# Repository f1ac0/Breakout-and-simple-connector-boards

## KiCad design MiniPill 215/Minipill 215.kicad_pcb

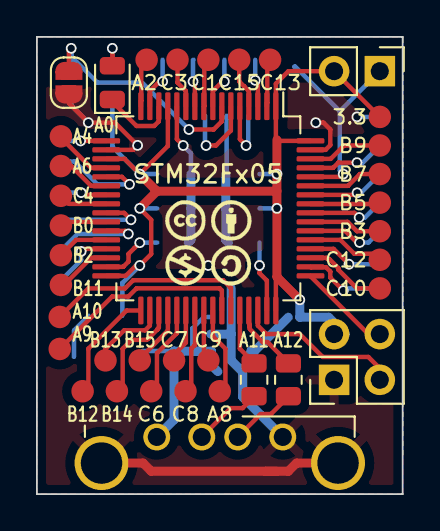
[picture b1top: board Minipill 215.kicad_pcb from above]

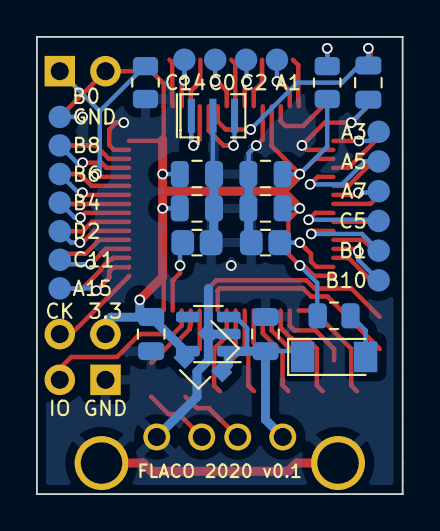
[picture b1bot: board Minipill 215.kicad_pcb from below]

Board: 2 copper layers, 20.3 x 25.4 mm, 71 parts (33 on the bottom side), 62 nets.

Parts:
C1, C2: 10u; C_0805_2012Metric
C3, C4, C5, C6, C7: 100n; C_0805_2012Metric
C10, C11: 2.2u; C_0805_2012Metric_shortable
D1: Zener 3.3v; D_MiniMELF
D2: LED; LED_0805_2012Metric
J1: Boot0; PinHeader_1x02_P2.54mm_Vertical
J2: USB_A; USB_A_female_THT_G54
J3: PROG; PinHeader_2x02_P2.54mm_Vertical
JP1: NRST; SolderJumper-2_P1.3mm_Open_RoundedPad1.0x1.5mm
MK5: License; CC_BY_NC_SA_square_silkscreen_4.8x4.8mm
R1, R2: 22; R_0805_2012Metric
R4: 4700; R_0805_2012Metric
R5: R_Small; R_0805_2012Metric
R6: 1k; R_0805_2012Metric
TP1, TP3, TP4, TP5, TP6, TP7, TP8, TP9, TP10, TP11, TP12, TP13, TP14, TP15, TP16, TP17, TP18, TP19, TP20, TP21, TP22, TP23, TP24, TP25, TP26, TP27, TP28, TP29, TP30, TP31, TP32, TP33, TP34, TP35, TP36, TP37, TP38, TP39, TP40, TP41, TP42, TP43, TP45, TP46: TP; Measurement_Point_Round-SMD-Pad_VerySmall
TP2: RX; Measurement_Point_Round-SMD-Pad_VerySmall
TP44: TX; Measurement_Point_Round-SMD-Pad_VerySmall
U1: STM32F105R8Tx; LQFP-64_10x10mm_P0.5mm
U2: SPX3819M5-L-3-3; SOT-23-5
U3: XC6206PxxxMR; SOT-23
Y1: 8MHz; Resonator_SMD_Murata_CSTxExxV-3Pin_3.0x1.1mm

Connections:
+3.3V: C2.1, C4.1, C5.1, C6.1, C7.1, J1.2, J3.2, R5.1, R6.1, TP45.1, U1.1 (VBAT), U1.13 (VDDA), U1.19 (VDD), U1.32 (VDD), U1.48 (VDD), U1.64 (VDD), U2.5 (OUT), U3.2 (VO)
+5V: C1.1, D1.1 (K), J2.1 (VBUS), U2.1 (IN), U2.3 (EN), U3.3 (VI)
BOOT0: J1.1, R4.1, U1.60 (BOOT0)
GROUND: C1.2, C2.2, C3.2, C4.2, C5.2, C6.2, C7.2, C10.2, C11.2, J2.4 (GND), J2.5 (Shield), J3.1, JP1.2 (B), R4.2, TP46.1, U1.12 (VSSA), U1.18 (VSS), U1.63 (VSS), U2.2 (GND), U3.1 (GND), Y1.2
JTCK-SWCLK: J3.4, U1.49 (PA14)
JTMS-SWDIO: J3.3, U1.46 (PA13)
LED: D2.1 (K), U1.14 (PA0)
NRST: C3.1, JP1.1 (A), U1.7 (NRST)
unnamed: U1.5 (PD0), Y1.1
unnamed: U1.6 (PD1), Y1.3
unnamed: C10.1, U1.31 (VSS)
unnamed: C11.1, U1.47 (VSS)
unnamed: D1.2 (A), R5.2
unnamed: D2.2 (A), R6.2
unnamed: J2.2 (D-), R2.1
unnamed: J2.3 (D+), R1.1
unnamed: TP1.1, U1.54 (PD2)
unnamed: TP3.1, U1.8 (PC0)
unnamed: TP4.1, U1.9 (PC1)
unnamed: TP5.1, U1.10 (PC2)
unnamed: TP6.1, U1.11 (PC3)
unnamed: TP7.1, U1.24 (PC4)
unnamed: TP8.1, U1.25 (PC5)
unnamed: TP9.1, U1.37 (PC6)
unnamed: TP10.1, U1.38 (PC7)
unnamed: TP11.1, U1.39 (PC8)
unnamed: TP12.1, U1.40 (PC9)
unnamed: TP13.1, U1.51 (PC10)
unnamed: TP14.1, U1.52 (PC11)
unnamed: TP15.1, U1.53 (PC12)
unnamed: TP16.1, U1.2 (PC13)
unnamed: TP17.1, U1.3 (PC14)
unnamed: TP18.1, U1.4 (PC15)
unnamed: TP19.1, U1.15 (PA1)
unnamed: TP20.1, U1.16 (PA2)
unnamed: TP21.1, U1.17 (PA3)
unnamed: TP22.1, U1.20 (PA4)
unnamed: TP23.1, U1.21 (PA5)
unnamed: TP24.1, U1.22 (PA6)
unnamed: TP25.1, U1.23 (PA7)
unnamed: TP26.1, U1.41 (PA8)
unnamed: TP27.1, U1.50 (PA15)
unnamed: TP28.1, U1.26 (PB0)
unnamed: TP29.1, U1.27 (PB1)
unnamed: TP30.1, U1.28 (PB2)
unnamed: TP31.1, U1.55 (PB3)
unnamed: TP32.1, U1.56 (PB4)
unnamed: TP33.1, U1.57 (PB5)
unnamed: TP34.1, U1.58 (PB6)
unnamed: TP35.1, U1.59 (PB7)
unnamed: TP36.1, U1.61 (PB8)
unnamed: TP37.1, U1.62 (PB9)
unnamed: TP38.1, U1.29 (PB10)
unnamed: TP39.1, U1.30 (PB11)
unnamed: TP40.1, U1.33 (PB12)
unnamed: TP41.1, U1.34 (PB13)
unnamed: TP42.1, U1.35 (PB14)
unnamed: TP43.1, U1.36 (PB15)
OTG_FS_DM: R2.2, U1.44 (PA11)
OTG_FS_DP: R1.2, U1.45 (PA12)
RX: TP2.1, U1.43 (PA10)
TX: TP44.1, U1.42 (PA9)

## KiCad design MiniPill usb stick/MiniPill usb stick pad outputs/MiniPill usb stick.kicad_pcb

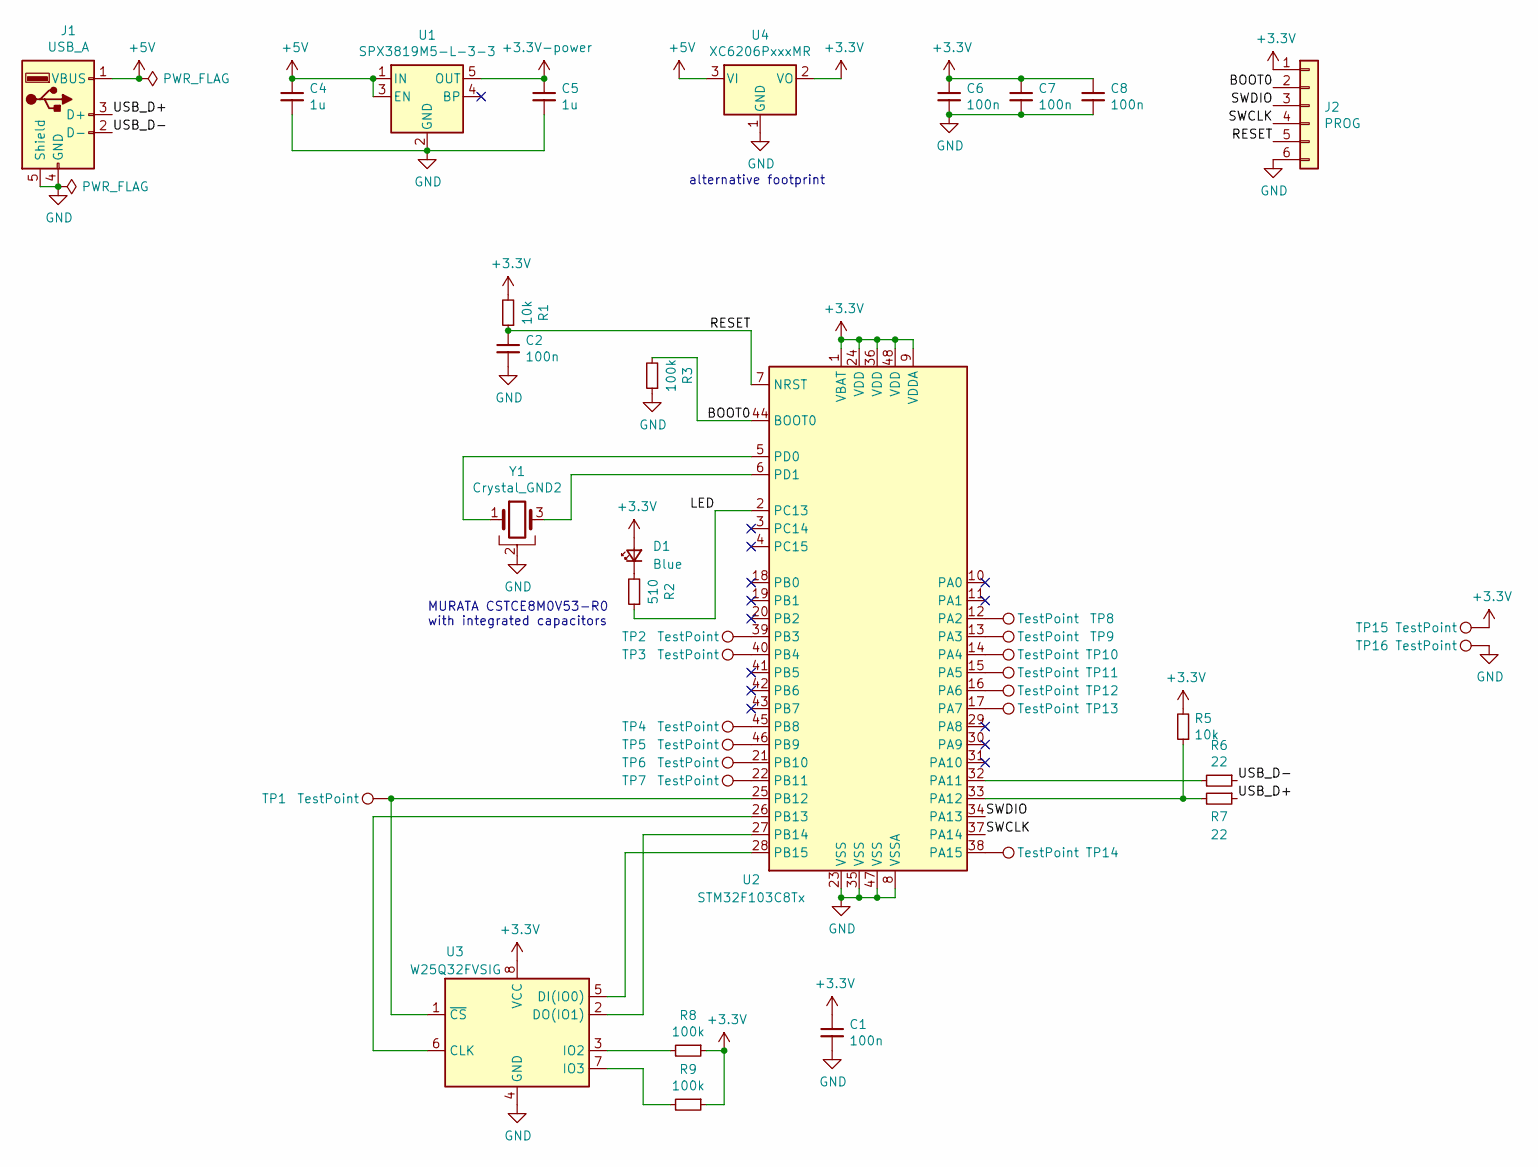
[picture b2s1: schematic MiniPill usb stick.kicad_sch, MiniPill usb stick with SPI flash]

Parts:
C1, C2, C6, C7, C8: 100n; C_0805_2012Metric
C4, C5: 1u; C_0805_2012Metric
D1: Blue; LED_0805_2012Metric
J1: USB_A; USB_A_CNCTech_1001-011-01101_Horizontal
J2: PROG; PinHeader_1x08_P2.54mm_Vertical
R1, R5: 10k; R_0805_2012Metric
R2: 510; R_0805_2012Metric
R3, R8, R9: 100k; R_0805_2012Metric
R6, R7: 22; R_0805_2012Metric
TP1, TP2, TP3, TP4, TP5, TP6, TP7, TP8, TP9, TP10, TP11, TP12, TP13, TP14, TP15, TP16: TestPoint; Measurement_Point_Round-SMD-Pad_VerySmall
U1: SPX3819M5-L-3-3; SOT-23-5
U2: STM32F103C8Tx; LQFP-48_7x7mm_P0.5mm
U3: W25Q32FVSIG; SOIC-8_5.23x5.23mm_P1.27mm
U4: XC6206PxxxMR; SOT-23
Y1: Crystal_GND2; Resonator_SMD_Murata_CSTxExxV-3Pin_3.0x1.1mm

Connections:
+5V: C4.1, J1.1 (VBUS), U1.1 (IN), U1.3 (EN), U4.3 (VI)
/BOOT0: J2.2, R3.2, U2.44 (BOOT0)
/LED: R2.1, U2.2 (PC13)
/RESET: C2.1, J2.5, R1.1, U2.7 (NRST)
/SWCLK: J2.4, U2.37 (PA14)
/SWDIO: J2.3, U2.34 (PA13)
/USB_D+: J1.3 (D+), R7.1
/USB_D-: J1.2 (D-), R6.1
GND: C1.2, C2.2, C4.2, C5.2, C6.2, C7.2, C8.2, J1.4 (GND), J1.5 (Shield), J2.6, R3.1, TP16.1, U1.2 (GND), U2.8 (VSSA), U2.23 (VSS), U2.35 (VSS), U2.47 (VSS), U3.4 (GND), U4.1 (GND), Y1.2
unnamed: D1.1 (K), R2.2
unnamed: R5.1, R7.2, U2.33 (PA12)
unnamed: R6.2, U2.32 (PA11)
unnamed: R8.2, U3.3 (IO2)
unnamed: R9.2, U3.7 (IO3)
unnamed: U2.5 (PD0), Y1.1
unnamed: U2.6 (PD1), Y1.3
unnamed: TP8.1, U2.12 (PA2)
unnamed: TP9.1, U2.13 (PA3)
unnamed: TP10.1, U2.14 (PA4)
unnamed: TP11.1, U2.15 (PA5)
unnamed: TP12.1, U2.16 (PA6)
unnamed: TP13.1, U2.17 (PA7)
unnamed: TP6.1, U2.21 (PB10)
unnamed: TP7.1, U2.22 (PB11)
unnamed: TP1.1, U2.25 (PB12), U3.1 (~CS)
unnamed: U2.26 (PB13), U3.6 (CLK)
unnamed: U2.27 (PB14), U3.2 (DO(IO1))
unnamed: U2.28 (PB15), U3.5 (DI(IO0))
unnamed: TP14.1, U2.38 (PA15)
unnamed: TP2.1, U2.39 (PB3)
unnamed: TP3.1, U2.40 (PB4)
unnamed: TP4.1, U2.45 (PB8)
unnamed: TP5.1, U2.46 (PB9)

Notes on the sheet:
alternative footprint
MURATA CSTCE8M0V53-R0 with integrated capacitors

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
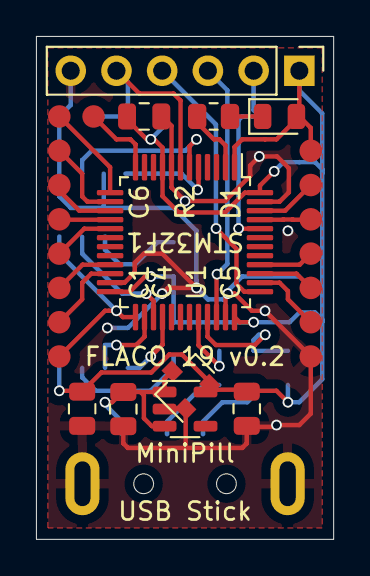
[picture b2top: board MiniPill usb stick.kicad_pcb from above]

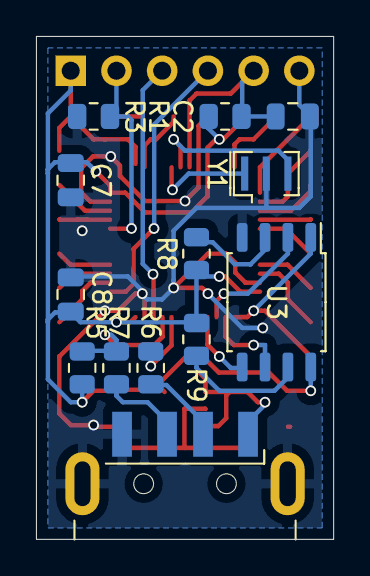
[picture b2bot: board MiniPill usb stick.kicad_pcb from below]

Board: 2 copper layers, 16.5 x 27.9 mm, 39 parts (13 on the bottom side), 34 nets.

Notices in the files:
MiniPill 215/Minipill 215.kicad_pcb:
FLACO 2019, licence of this PCB is CC-BY-NC-SA
MiniPill usb stick/MiniPill usb stick castellated outputs/MiniPill usb stick.kicad_sch:
FLACO 2019, licence of this schematic is CC-BY-NC-SA
